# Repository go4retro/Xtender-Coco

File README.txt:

TANDY Color Computer/Dragon cartridge port extender
Copyright (C) 2018 Jim Brain

These files are free designs; you can redistribute them and/or modify
them under the terms of the Creative Commons Attribution-ShareAlike 
4.0 International License.

You should have received a copy of the license along with this
work. If not, see <http://creativecommons.org/licenses/by-sa/4.0/>.

These files are distributed in the hope that they will be useful,
but WITHOUT ANY WARRANTY; without even the implied warranty of
MERCHANTABILITY or FITNESS FOR A PARTICULAR PURPOSE.  See the
license for more details.

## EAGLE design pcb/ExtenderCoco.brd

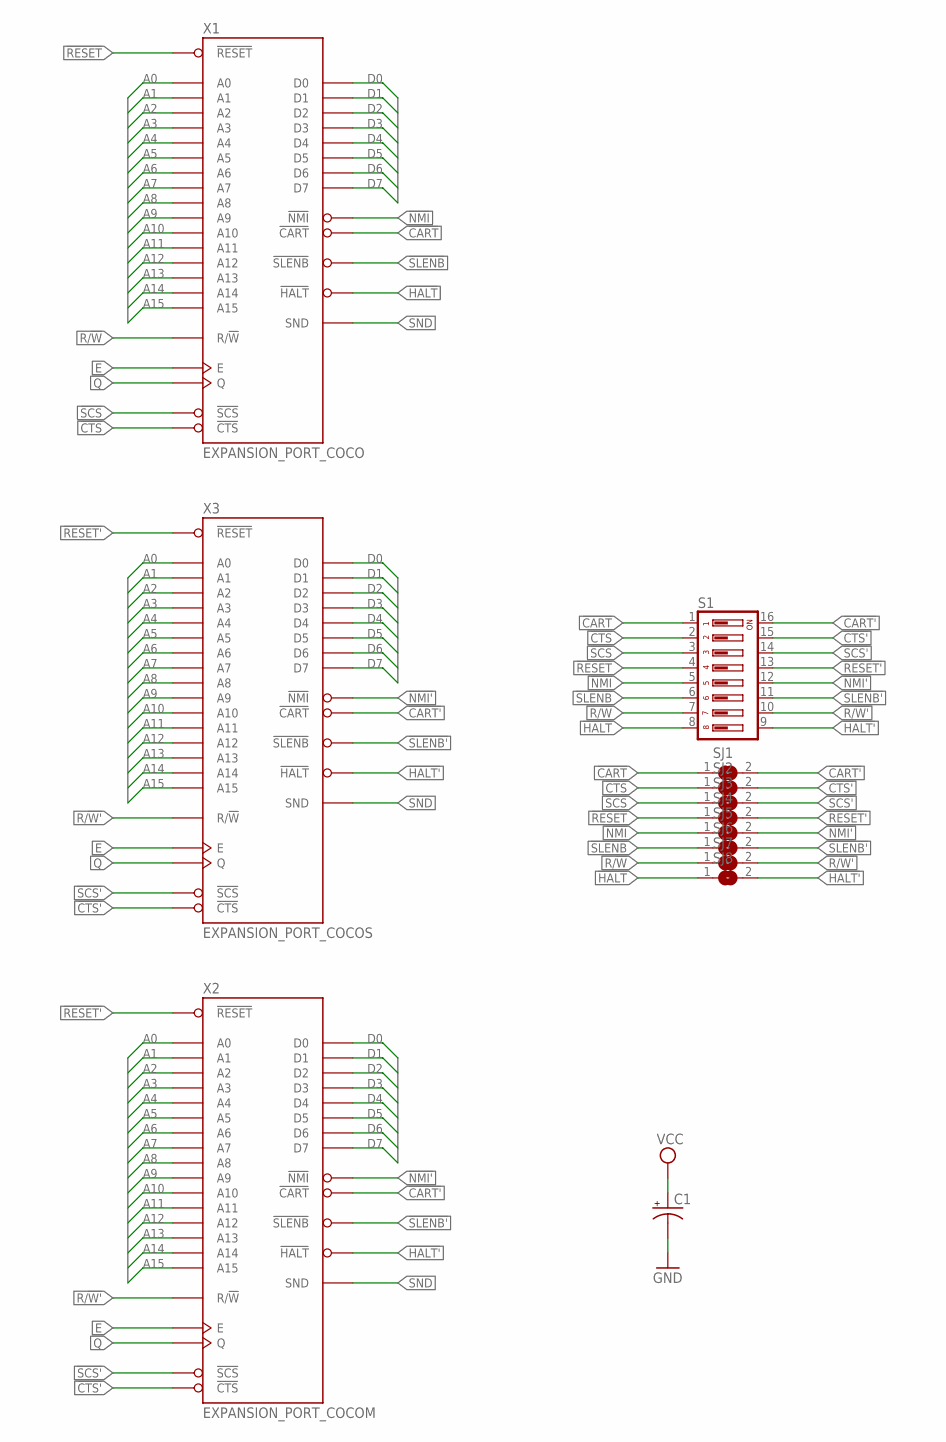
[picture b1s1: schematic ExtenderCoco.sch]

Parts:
C1: CPOL-USE2-5; E2-5
S1: DP08; DP-08
SJ1, SJ2, SJ3, SJ4, SJ5, SJ6, SJ7, SJ8: SJ
X1: EXPANSION_PORT_COCO; MA20-2
X2: EXPANSION_PORT_COCOM; FE20-2
X3: EXPANSION_PORT_COCOS; MA20-2_SHORT

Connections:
!CART: S1.1, SJ1.1, X1.8 (!CART)
!CART': S1.16, SJ1.2, X2.8 (!CART), X3.8 (!CART)
!CTS: S1.2, SJ2.1, X1.32 (!CTS)
!CTS': S1.15, SJ2.2, X2.32 (!CTS), X3.32 (!CTS)
!HALT: S1.8, SJ8.1, X1.3 (!HALT)
!HALT': S1.9, SJ8.2, X2.3 (!HALT), X3.3 (!HALT)
!NMI: S1.5, SJ5.1, X1.4 (!NMI)
!NMI': S1.12, SJ5.2, X2.4 (!NMI), X3.4 (!NMI)
!RESET: S1.4, SJ4.1, X1.5 (!RESET)
!RESET': S1.13, SJ4.2, X2.5 (!RESET), X3.5 (!RESET)
!SCS: S1.3, SJ3.1, X1.36 (!SCS)
!SCS': S1.14, SJ3.2, X2.36 (!SCS), X3.36 (!SCS)
!SLENB: S1.6, SJ6.1, X1.40 (!SLENB)
!SLENB': S1.11, SJ6.2, X2.40 (!SLENB), X3.40 (!SLENB)
+12V: X1.2 (+12V), X2.2 (+12V), X3.2 (+12V)
-12V: X1.1 (-12V), X2.1 (-12V), X3.1 (-12V)
A0: X1.19 (A0), X2.19 (A0), X3.19 (A0)
A1: X1.20 (A1), X2.20 (A1), X3.20 (A1)
A2: X1.21 (A2), X2.21 (A2), X3.21 (A2)
A3: X1.22 (A3), X2.22 (A3), X3.22 (A3)
A4: X1.23 (A4), X2.23 (A4), X3.23 (A4)
A5: X1.24 (A5), X2.24 (A5), X3.24 (A5)
A6: X1.25 (A6), X2.25 (A6), X3.25 (A6)
A7: X1.26 (A7), X2.26 (A7), X3.26 (A7)
A8: X1.27 (A8), X2.27 (A8), X3.27 (A8)
A9: X1.28 (A9), X2.28 (A9), X3.28 (A9)
A10: X1.29 (A10), X2.29 (A10), X3.29 (A10)
A11: X1.30 (A11), X2.30 (A11), X3.30 (A11)
A12: X1.31 (A12), X2.31 (A12), X3.31 (A12)
A13: X1.37 (A13), X2.37 (A13), X3.37 (A13)
A14: X1.38 (A14), X2.38 (A14), X3.38 (A14)
A15: X1.39 (A15), X2.39 (A15), X3.39 (A15)
D0: X1.10 (D0), X2.10 (D0), X3.10 (D0)
D1: X1.11 (D1), X2.11 (D1), X3.11 (D1)
D2: X1.12 (D2), X2.12 (D2), X3.12 (D2)
D3: X1.13 (D3), X2.13 (D3), X3.13 (D3)
D4: X1.14 (D4), X2.14 (D4), X3.14 (D4)
D5: X1.15 (D5), X2.15 (D5), X3.15 (D5)
D6: X1.16 (D6), X2.16 (D6), X3.16 (D6)
D7: X1.17 (D7), X2.17 (D7), X3.17 (D7)
E: X1.6 (E), X2.6 (E), X3.6 (E)
GND: C1.-, X1.33 (GND), X1.34 (GND), X2.33 (GND), X2.34 (GND), X3.33 (GND), X3.34 (GND)
Q: X1.7 (Q), X2.7 (Q), X3.7 (Q)
R/!W: S1.7, SJ7.1, X1.18 (R/!W)
R/!W': S1.10, SJ7.2, X2.18 (R/!W), X3.18 (R/!W)
SND: X1.35 (SND), X2.35 (SND), X3.35 (SND)
VCC: C1.+, X1.9 (VCC), X2.9 (VCC), X3.9 (VCC)

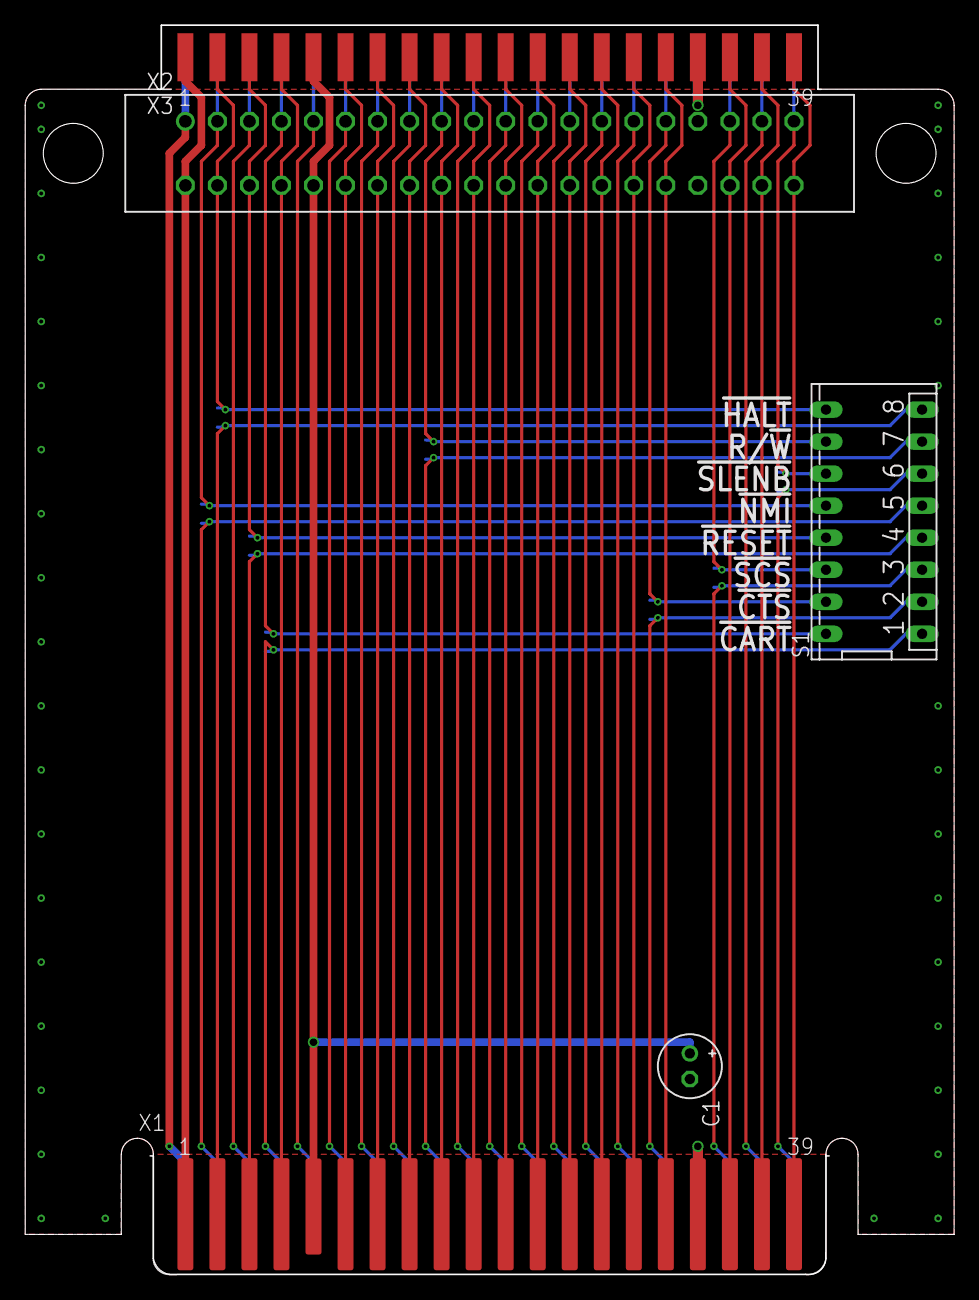
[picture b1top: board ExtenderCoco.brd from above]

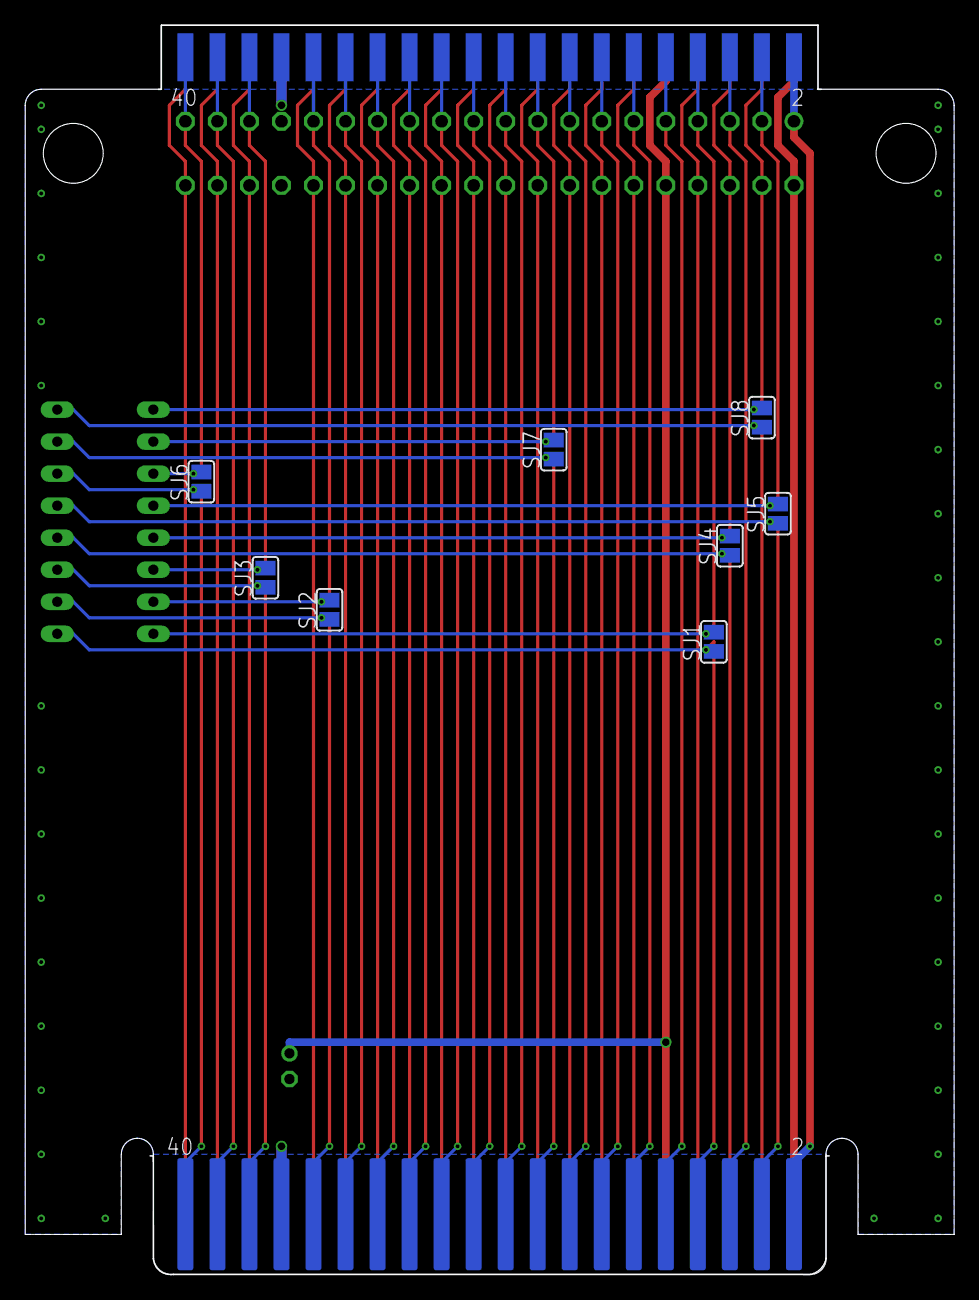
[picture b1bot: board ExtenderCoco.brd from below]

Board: 2 copper layers, 73.6 x 99.1 mm, 13 parts (8 on the bottom side), 47 nets.

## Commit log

2018-03-11 Updated license
2020-01-11 Cart port connector was too narrow...
